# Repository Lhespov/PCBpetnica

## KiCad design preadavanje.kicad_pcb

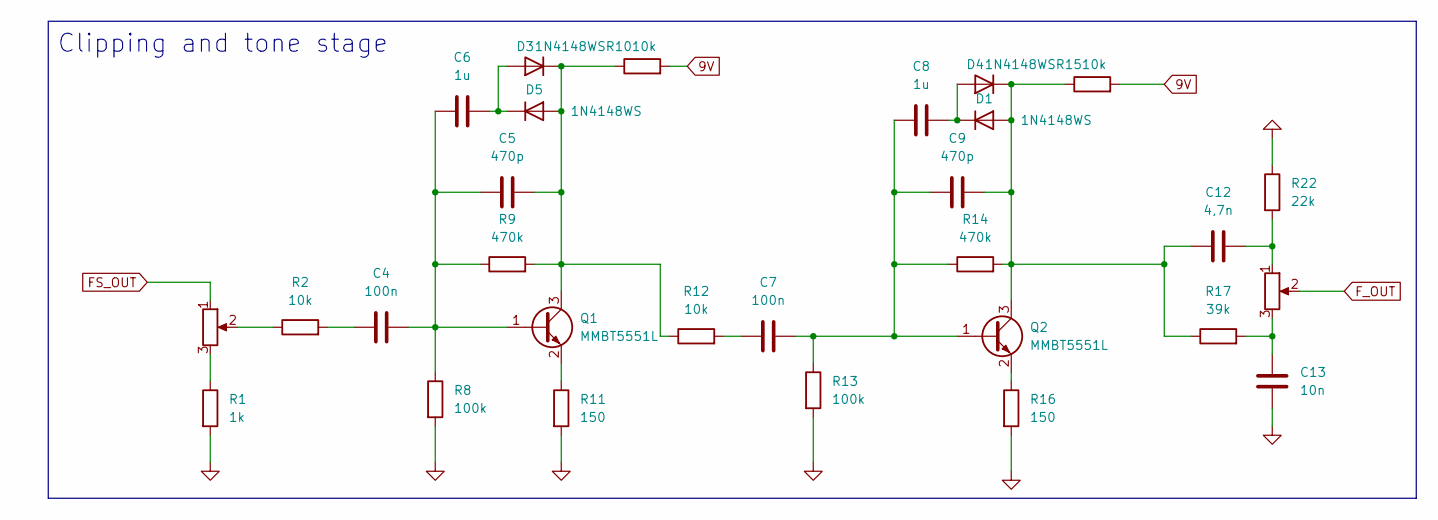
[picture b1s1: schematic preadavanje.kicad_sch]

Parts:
C4, C7: 100n; C_0805_2012Metric
C5, C9: 470p; C_0805_2012Metric
C6, C8: 1u; C_0805_2012Metric
C12: 4,7n; C_0805_2012Metric
C13: 10n; C_0805_2012Metric
D1, D3, D4, D5: 1N4148WS; D_SOD-323
Q1, Q2: MMBT5551L; SOT-23
R1: 1k; R_0805_2012Metric
R2, R10, R12, R15: 10k; R_0805_2012Metric
R8, R13: 100k; R_0805_2012Metric
R9, R14: 470k; R_0805_2012Metric
R11, R16: 150; R_0805_2012Metric
R17: 39k; R_0805_2012Metric
R22: 22k; R_0805_2012Metric
RV1, RV2: R_Potentiometer; Potentiometer_Alpha_RD901F-40-00D_Single_Vertical

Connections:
9V: R10.2, R15.2
FS_OUT: RV1.1
F_OUT: RV2.2
GND: C13.2, R1.2, R8.2, R11.2, R13.2, R16.2, R22.1
unnamed: C4.1, R2.2
unnamed: C7.1, R12.2
unnamed: C12.2, R22.2, RV2.1
unnamed: C13.1, R17.2, RV2.3
unnamed: C9.2, C12.1, D1.2 (A), D4.1 (K), Q2.3 (C), R14.2, R15.1, R17.1
unnamed: C8.2, D1.1 (K), D4.2 (A)
unnamed: C6.2, D3.2 (A), D5.1 (K)
unnamed: C5.2, D3.1 (K), D5.2 (A), Q1.3 (C), R9.2, R10.1, R12.1
unnamed: C4.2, C5.1, C6.1, Q1.1 (B), R8.1, R9.1
unnamed: Q1.2 (E), R11.1
unnamed: C7.2, C8.1, C9.1, Q2.1 (B), R13.1, R14.1
unnamed: Q2.2 (E), R16.1
unnamed: R1.1, RV1.3
unnamed: R2.1, RV1.2

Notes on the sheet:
Clipping and tone stage

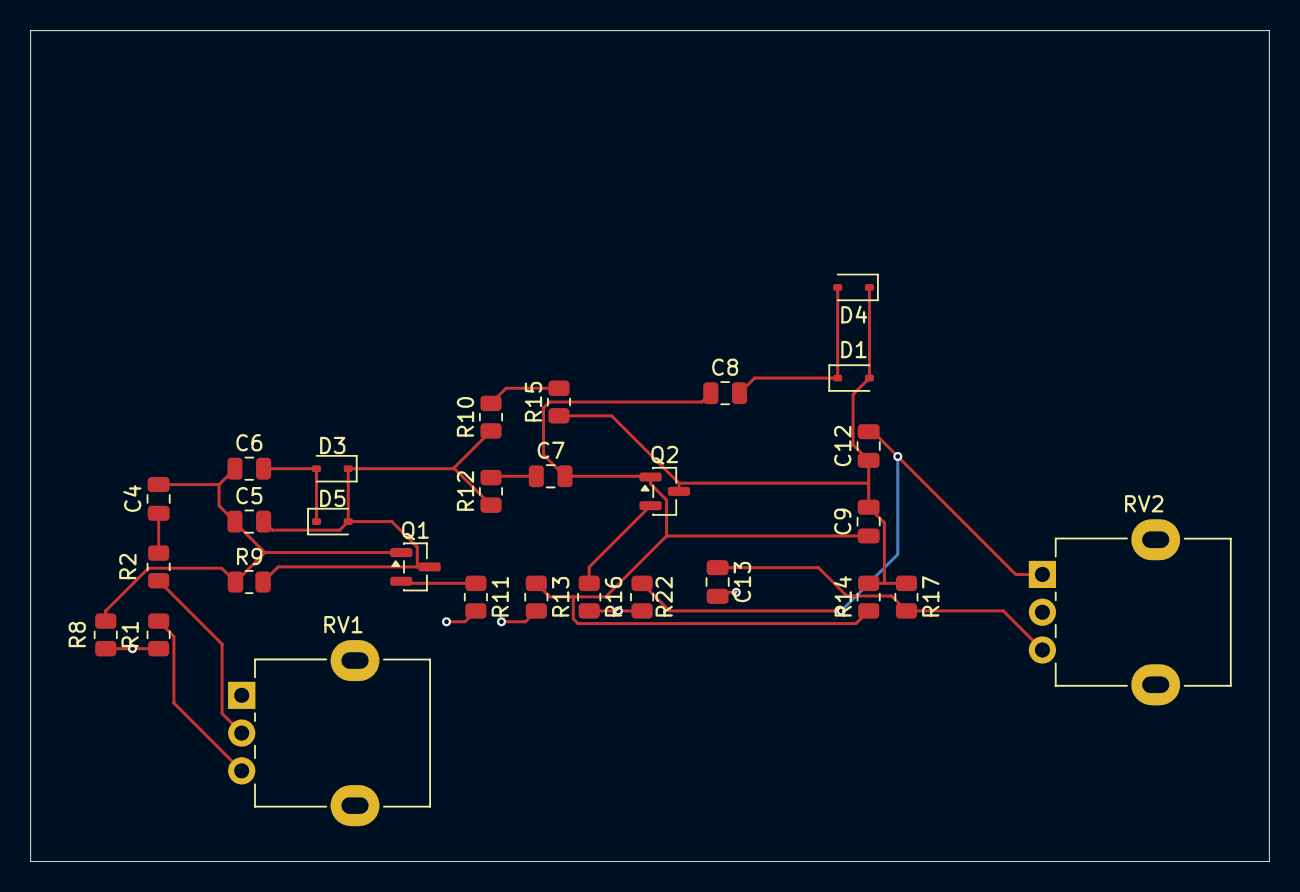
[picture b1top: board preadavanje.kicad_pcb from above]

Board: 2 copper layers, 82.0 x 55.0 mm, 29 parts (0 on the bottom side), 16 nets.
